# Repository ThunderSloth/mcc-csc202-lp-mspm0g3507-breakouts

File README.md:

# MCC CSC202 — LP-MSPM0G3507 Breakout Boards

KiCad project files and fabrication outputs for **breakout boards based on the TI MSPM0G3507 LaunchPad footprint** designed to fit dual- and triple-breadboard platforms (e.g., Jameco ValuePro) for use in Monroe Community College’s CSC-202 course.

---

## ℹ️  Hardware Documentation (MkDocs)

- **[Live Docs Site (renders + PDFs + iBOM + fabrication zips](https://thundersloth.github.io/mcc-csc202-lp-mspm0g3507-breakouts/)**  

---

## 📁 Boards

### **2-Term Breakout**
- [Docs Page](https://thundersloth.github.io/mcc-csc202-lp-mspm0g3507-breakouts/2-term/)
- [Download Gerbers (ZIP)](https://thundersloth.github.io/mcc-csc202-lp-mspm0g3507-breakouts/artifacts/2-term/fab/CSC202_LP_MSPM0G3507_2TERM_BREAKOUT_fab.zip)

---

### **3-Term Breakout**
- [Docs Page](https://thundersloth.github.io/mcc-csc202-lp-mspm0g3507-breakouts/3-term/)
- [Download Gerbers (ZIP)](https://thundersloth.github.io/mcc-csc202-lp-mspm0g3507-breakouts/artifacts/3-term/fab/CSC202_LP_MSPM0G3507_3TERM_BREAKOUT_fab.zip)

---

### **LED Display Module**
The CSC-202 LED Module is a visual output board featuring an 8-LED bar graph and a 4-digit seven-segment display. The LEDs and display segments can be driven either directly via GPIO (current sinking) or through an SPI shift register interface. A jumper shunt selects the control mode, allowing the module to demonstrate both parallel GPIO control and serial output expansion. The board is designed to plug directly into a standard breadboard for easy prototyping and lab use.
- [Docs Page](https://thundersloth.github.io/mcc-csc202-lp-mspm0g3507-breakouts/led-module/)
- [Download Gerbers (ZIP)](https://thundersloth.github.io/mcc-csc202-lp-mspm0g3507-breakouts/artifacts/led-module/fab/CSC202_LED_MODULE_fab.zip.zip)

---

### **DIP Switch / Pushbutton Module**
The CSC-202 DIP Switch / Pushbutton Module provides four digital input channels, each connected to both a DIP switch and a momentary pushbutton. This allows testing of both persistent and transient inputs on shared GPIO lines. An additional analog input is provided via an onboard potentiometer, which can be enabled or disconnected using a dedicated DIP switch. The module is designed for direct breadboard use and serves as a simple, reusable input interface for labs and debugging.

- [Docs Page](https://thundersloth.github.io/mcc-csc202-lp-mspm0g3507-breakouts/dipsw-module/)
- [Download Gerbers (ZIP)](https://thundersloth.github.io/mcc-csc202-lp-mspm0g3507-breakouts/artifacts/dipsw-module/fab/CSC202_DIPSW_fab.zip)

---

## 🛠 Repo Layout

- `hardware/pcb/kicad/` → KiCad source projects (per-board)
- `hardware/kibot/` → KiBot config
- `outputs/` → local generated artifacts (ignored/regen as needed)
- `docs/` + `docs/artifacts/` → MkDocs site + published artifacts

---

## 🔄 Generating outputs locally

If you want to regenerate all artifacts with KiBot + sync them into MkDocs:

```bash
make
```

---

## 📸 Fabricated Board Photos

<p align="center">
    <strong>3-Term Breakout</strong><br>
  
</p>

<p align="center">
  <strong>LED Display Module</strong><br>
  
</p>

---

## 📐 Example Breadboard Application

The diagram below shows an example application implemented on a 3-terminal breadboard.

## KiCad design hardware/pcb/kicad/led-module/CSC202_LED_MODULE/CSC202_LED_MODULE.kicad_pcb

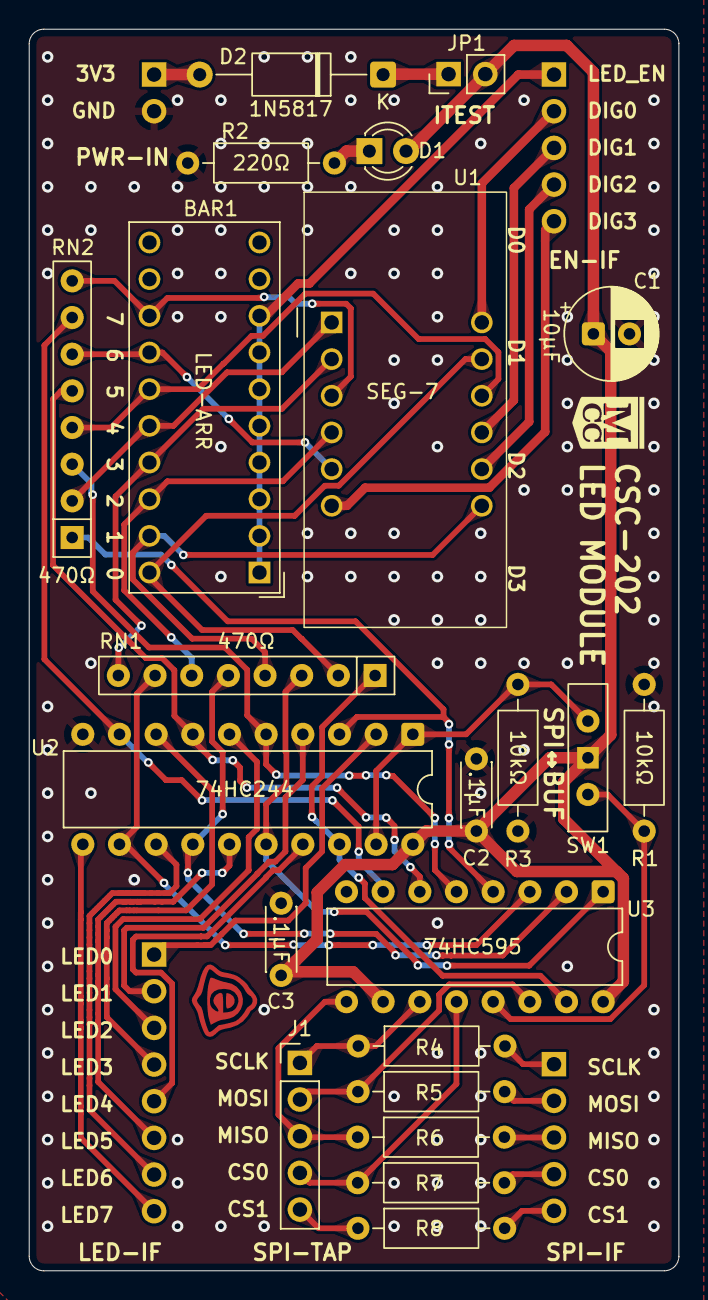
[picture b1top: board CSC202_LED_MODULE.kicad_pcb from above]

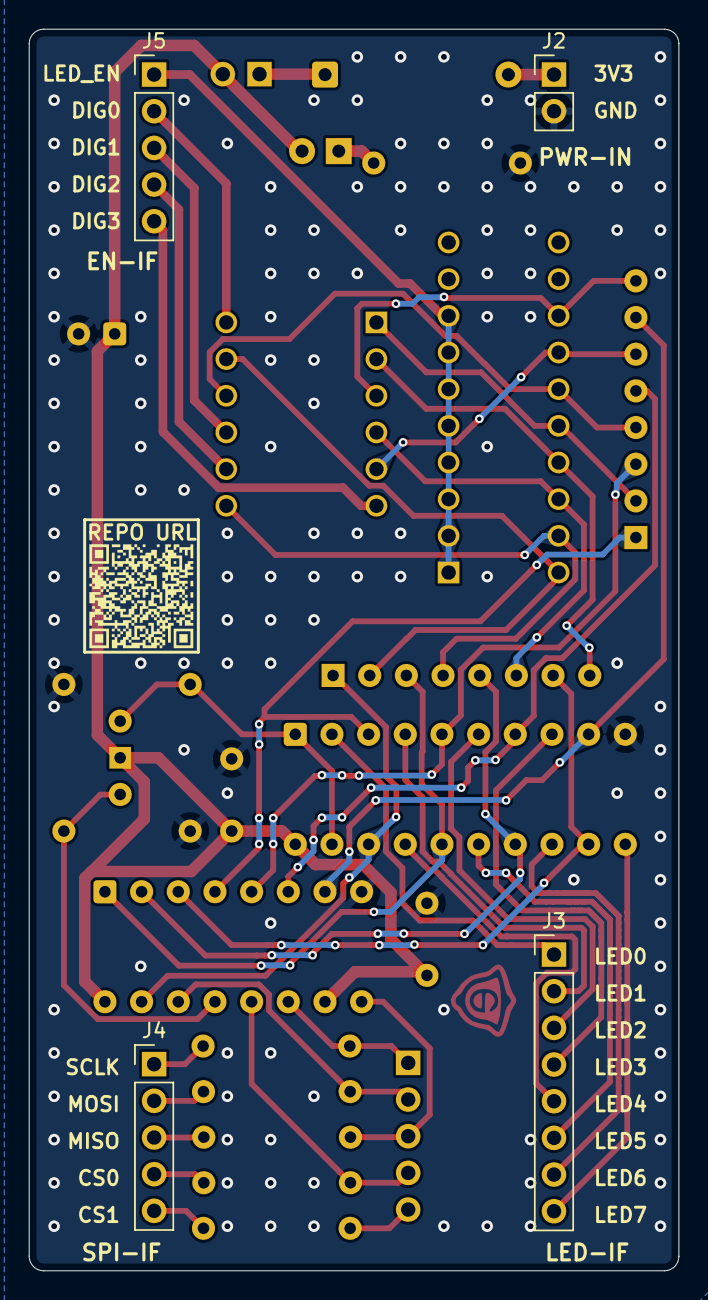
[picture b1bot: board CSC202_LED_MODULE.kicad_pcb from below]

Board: 2 copper layers, 45.0 x 86.0 mm, 26 parts (4 on the bottom side), 46 nets.

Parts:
BAR1: HDSP-4830_2; HDSP-4830
C1: 10µF; CP_Radial_D6.3mm_P2.50mm
C2, C3: .1µF; C_Disc_D4.3mm_W1.9mm_P5.00mm
D1: PWR; LED_D3.0mm
D2: 1N5817; D_A-405_P12.70mm_Horizontal
J1: SPI-TAP; PinHeader_1x05_P2.54mm_Vertical
J2: PWR-IN; PinHeader_1x02_P2.54mm_Vertical
J3: LED-IF; PinHeader_1x08_P2.54mm_Vertical
J4: SPI-IF; PinHeader_1x05_P2.54mm_Vertical
J5: EN-IF; PinHeader_1x05_P2.54mm_Vertical
JP1: TEST-PT; PinHeader_1x02_P2.54mm_Vertical
R1, R3: 10kΩ; R_Axial_DIN0207_L6.3mm_D2.5mm_P10.16mm_Horizontal
R2: 220Ω; R_Axial_DIN0207_L6.3mm_D2.5mm_P10.16mm_Horizontal
R4, R5, R6, R7, R8: 33Ω; R_Axial_DIN0207_L6.3mm_D2.5mm_P10.16mm_Horizontal
RN1, RN2: 470Ω; R_Array_SIP8
SW1: BUF↔SPI; SW_Slide-03_Wuerth-WS-SLTV_10x2.5x6.4_P2.54mm
U1: CA56-12SEKWA; CL3641BH
U2: 74HC244; DIP-20_W7.62mm
U3: 74HC595; DIP-16_W7.62mm

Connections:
+3V3: C1.1, C2.2, C3.2, D1.2 (A), JP1.2 (B), SW1.2 (B), U2.20 (VCC), U3.10 (~SRCLR), U3.16 (VCC)
/!BUF_EN: R3.1, SW1.3 (C), U2.1 (1OE), U2.19 (2OE)
/!SPI_EN: R1.1, SW1.1 (A), U3.13 (~OE)
/CLK: J1.1, R4.1, U3.11 (SRCLK)
/CLK_EXT: J4.1, R4.2
/CS0: J1.4, R7.1, U3.12 (RCLK)
/CS0_EXT: J4.4, R7.2
/CS1: J1.5, R8.1
/CS1_EXT: J4.5, R8.2
/DIG0: J5.2, U1.12 (CA1)
/DIG1: J5.3, U1.9 (CA2)
/DIG2: J5.4, U1.8 (CA3)
/DIG3: J5.5, U1.6 (CA4)
/LED_BUS0: RN1.1 (R1.1), U2.18 (1Y0), U3.15 (QA)
/LED_BUS1: RN1.3 (R2.1), U2.16 (1Y1), U3.1 (QB)
/LED_BUS2: RN1.5 (R3.1), U2.14 (1Y2), U3.2 (QC)
/LED_BUS3: RN1.7 (R4.1), U2.12 (1Y3), U3.3 (QD)
/LED_BUS4: RN2.1 (R1.1), U2.3 (2Y0), U3.4 (QE)
/LED_BUS5: RN2.3 (R2.1), U2.5 (2Y1), U3.5 (QF)
/LED_BUS6: RN2.5 (R3.1), U2.7 (2Y2), U3.6 (QG)
/LED_BUS7: RN2.7 (R4.1), U2.9 (2Y3), U3.7 (QH)
/LED_EN: BAR1.1 (A), BAR1.2 (A), BAR1.3 (A), BAR1.4 (A), BAR1.5 (A), BAR1.6 (A), BAR1.7 (A), BAR1.8 (A), J5.1
/LED_EXT0: J3.1, U2.2 (1A0)
/LED_EXT1: J3.2, U2.4 (1A1)
/LED_EXT2: J3.3, U2.6 (1A2)
/LED_EXT3: J3.4, U2.8 (1A3)
/LED_EXT4: J3.5, U2.17 (2A0)
/LED_EXT5: J3.6, U2.15 (2A1)
/LED_EXT6: J3.7, U2.13 (2A2)
/LED_EXT7: J3.8, U2.11 (2A3)
/LED_R0: BAR1.20 (K), RN1.2 (R1.2), U1.11 (a)
/LED_R1: BAR1.19 (K), RN1.4 (R2.2), U1.7 (b)
/LED_R2: BAR1.18 (K), RN1.6 (R3.2), U1.4 (c)
/LED_R3: BAR1.17 (K), RN1.8 (R4.2), U1.2 (d)
/LED_R4: BAR1.16 (K), RN2.2 (R1.2), U1.1 (e)
/LED_R5: BAR1.15 (K), RN2.4 (R2.2), U1.10 (f)
/LED_R6: BAR1.14 (K), RN2.6 (R3.2), U1.5 (g)
/LED_R7: BAR1.13 (K), RN2.8 (R4.2), U1.3 (DPX)
/MISO: J1.3, R6.1, U3.9 (QH')
/MISO_EXT: J4.3, R6.2
/MOSI: J1.2, R5.1, U3.14 (SER)
/MOSI_EXT: J4.2, R5.2
GND: C1.2, C2.1, C3.1, J2.2, R1.2, R2.1, R3.2, U2.10 (GND), U3.8 (GND)
unnamed: D1.1 (K), R2.2
unnamed: D2.2 (A), J2.1
unnamed: D2.1 (K), JP1.1 (A)

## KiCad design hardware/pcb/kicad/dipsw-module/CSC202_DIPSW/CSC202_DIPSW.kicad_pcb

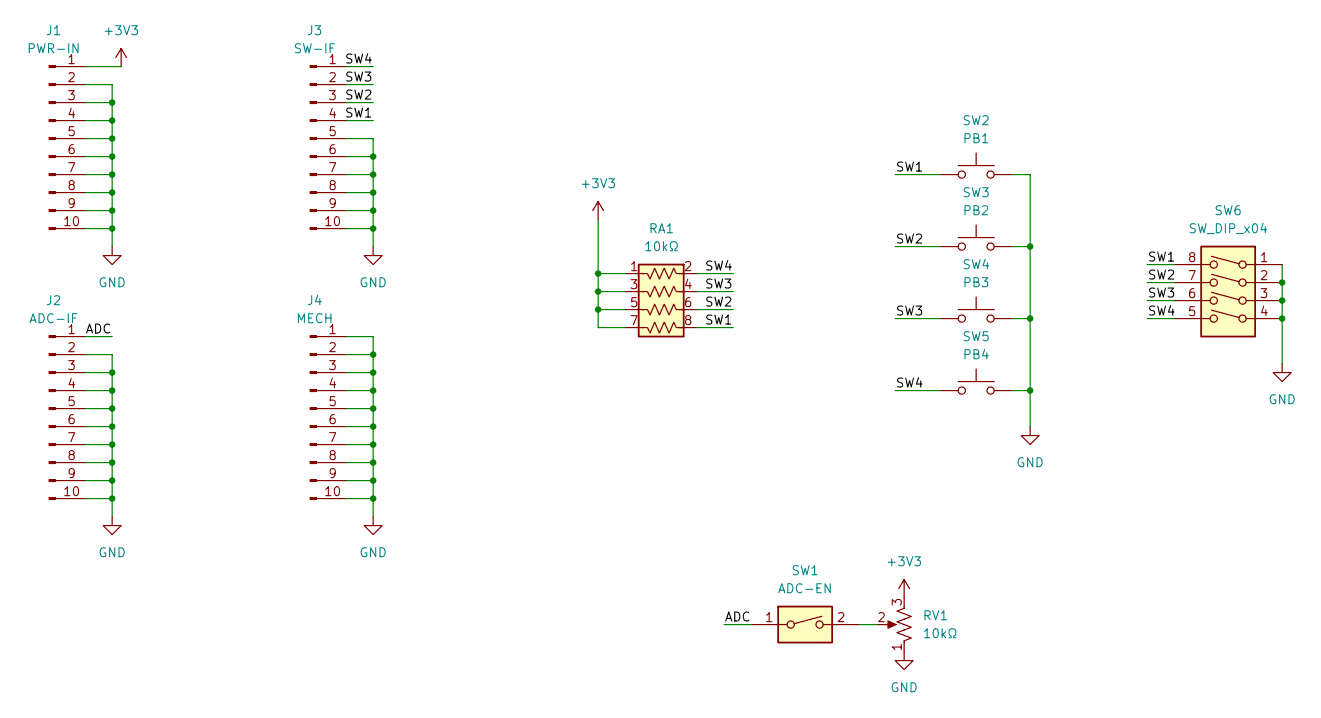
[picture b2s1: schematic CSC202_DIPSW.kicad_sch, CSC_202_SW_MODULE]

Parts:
J1: PWR-IN; PinHeader_1x10_P2.54mm_Vertical
J2: ADC-IF; PinHeader_1x10_P2.54mm_Vertical
J3: SW-IF; PinHeader_1x10_P2.54mm_Vertical
J4: MECH; PinHeader_1x10_P2.54mm_Vertical
RA1: 10kΩ; R_Array_SIP8
RV1: 10kΩ; Potentiometer_Piher_T-16H_Single_Horizontal
SW1: ADC-EN; SW_DIP_SPSTx01_Slide_9.78x4.72mm_W7.62mm_P2.54mm
SW2: PB1; SW_PUSH_6mm
SW3: PB2; SW_PUSH_6mm
SW4: PB3; SW_PUSH_6mm
SW5: PB4; SW_PUSH_6mm
SW6: SW_DIP_x04; SW_DIP_SPSTx04_Slide_9.78x12.34mm_W7.62mm_P2.54mm

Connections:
+3V3: J1.1, RA1.1 (R1a), RA1.3 (R2a), RA1.5 (R3a), RA1.7 (R4a), RV1.3 (1)
/ADC: J2.1, SW1.1
/SW1: J3.4, RA1.8 (R4b), SW2.2, SW6.8
/SW2: J3.3, RA1.6 (R3b), SW3.2, SW6.7
/SW3: J3.2, RA1.4 (R2b), SW4.2, SW6.6
/SW4: J3.1, RA1.2 (R1b), SW5.2, SW6.5
GND: J1.2, J1.3, J1.4, J1.5, J1.6, J1.7, J1.8, J1.9, J1.10, J2.2, J2.3, J2.4, J2.5, J2.6, J2.7, J2.8, J2.9, J2.10, J3.5, J3.6, J3.7, J3.8, J3.9, J3.10, J4.1, J4.2, J4.3, J4.4, J4.5, J4.6, J4.7, J4.8, J4.9, J4.10, RV1.1 (3), SW2.1, SW3.1, SW4.1, SW5.1, SW6.1, SW6.2, SW6.3, SW6.4
unnamed: RV1.2, SW1.2

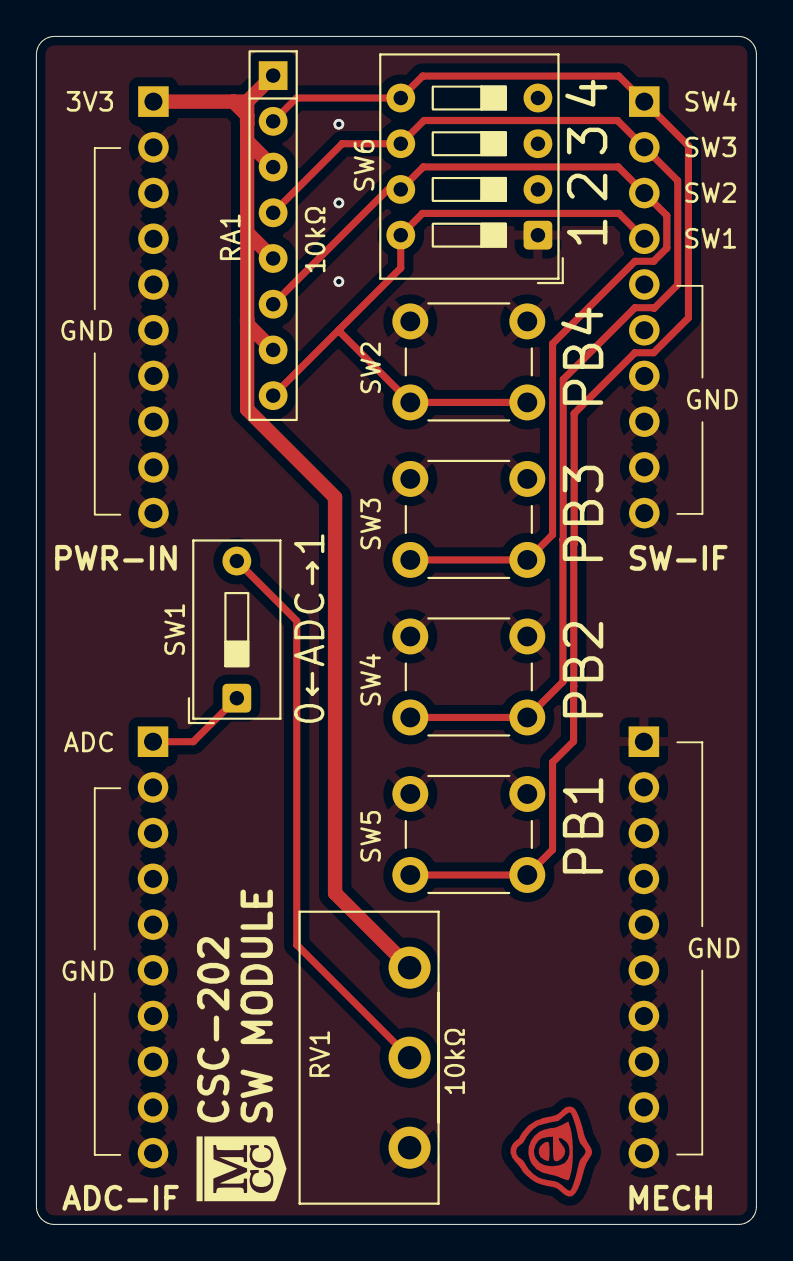
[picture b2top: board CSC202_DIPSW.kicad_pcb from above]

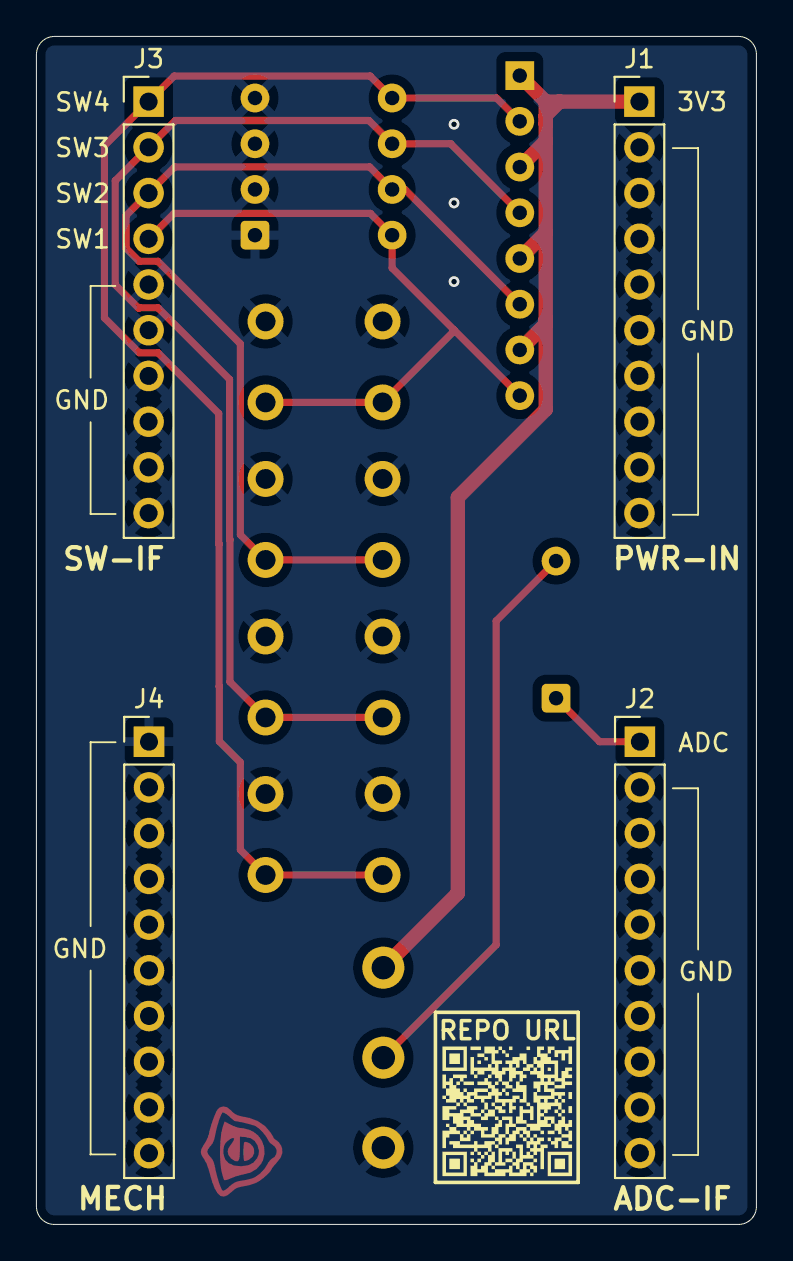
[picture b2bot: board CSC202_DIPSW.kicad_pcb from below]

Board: 2 copper layers, 40.0 x 66.0 mm, 12 parts (4 on the bottom side), 8 nets.

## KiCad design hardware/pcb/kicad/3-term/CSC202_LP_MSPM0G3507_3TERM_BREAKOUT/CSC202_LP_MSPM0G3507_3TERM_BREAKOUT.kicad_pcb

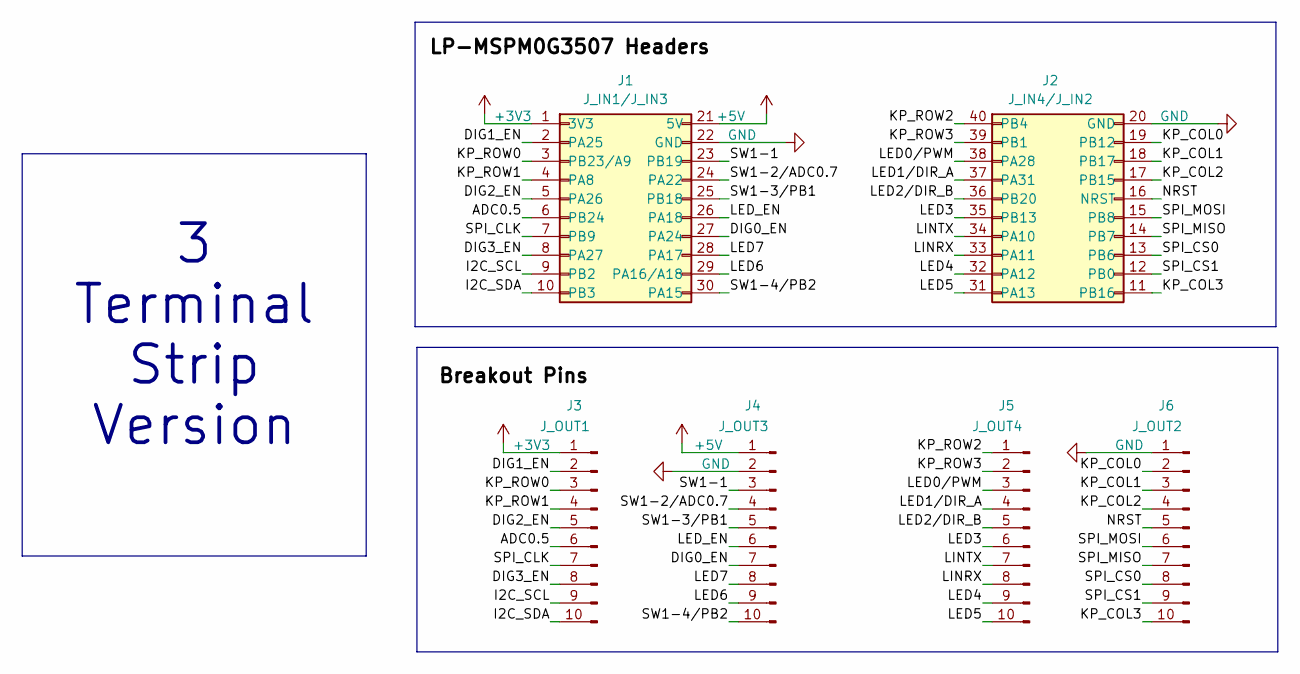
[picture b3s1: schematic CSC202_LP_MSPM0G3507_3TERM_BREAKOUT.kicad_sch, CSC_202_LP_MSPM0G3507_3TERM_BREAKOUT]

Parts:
J1: J_IN1/J_IN3; PinHeader_2x10_P2.54mm_Vertical
J2: J_IN4/J_IN2; PinHeader_2x10_P2.54mm_Vertical
J3: J_OUT1; PinHeader_1x10_P2.54mm_Vertical
J4: J_OUT3; PinHeader_1x10_P2.54mm_Vertical
J5: J_OUT4; PinHeader_1x10_P2.54mm_Vertical
J6: J_OUT2; PinHeader_1x10_P2.54mm_Vertical

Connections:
+3V3: J1.1 (3V3), J3.1
+5V: J1.21 (5V), J4.1
/ADC0.5: J1.6 (PB24), J3.6
/DIG0_EN: J1.27 (PA24), J4.7
/DIG1_EN: J1.2 (PA25), J3.2
/DIG2_EN: J1.5 (PA26), J3.5
/DIG3_EN: J1.8 (PA27), J3.8
/I2C_SCL: J1.9 (PB2), J3.9
/I2C_SDA: J1.10 (PB3), J3.10
/KP_COL0: J2.19 (PB12), J6.2
/KP_COL1: J2.18 (PB17), J6.3
/KP_COL2: J2.17 (PB15), J6.4
/KP_COL3: J2.11 (PB16), J6.10
/KP_ROW0: J1.3 (PB23/A9), J3.3
/KP_ROW1: J1.4 (PA8), J3.4
/KP_ROW2: J2.40 (PB4), J5.1
/KP_ROW3: J2.39 (PB1), J5.2
/LED0/PWM: J2.38 (PA28), J5.3
/LED1/DIR_A: J2.37 (PA31), J5.4
/LED2/DIR_B: J2.36 (PB20), J5.5
/LED3: J2.35 (PB13), J5.6
/LED4: J2.32 (PA12), J5.9
/LED5: J2.31 (PA13), J5.10
/LED6: J1.29 (PA16/A18), J4.9
/LED7: J1.28 (PA17), J4.8
/LED_EN: J1.26 (PA18), J4.6
/LINRX: J2.33 (PA11), J5.8
/LINTX: J2.34 (PA10), J5.7
/NRST: J2.16 (NRST), J6.5
/SPI_CLK: J1.7 (PB9), J3.7
/SPI_CS0: J2.13 (PB6), J6.8
/SPI_CS1: J2.12 (PB0), J6.9
/SPI_MISO: J2.14 (PB7), J6.7
/SPI_MOSI: J2.15 (PB8), J6.6
/SW1-1: J1.23 (PB19), J4.3
/SW1-2/ADC0.7: J1.24 (PA22), J4.4
/SW1-3/PB1: J1.25 (PB18), J4.5
/SW1-4/PB2: J1.30 (PA15), J4.10
GND: J1.22 (GND), J2.20 (GND), J4.2, J6.1

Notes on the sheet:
3 Terminal Strip Version

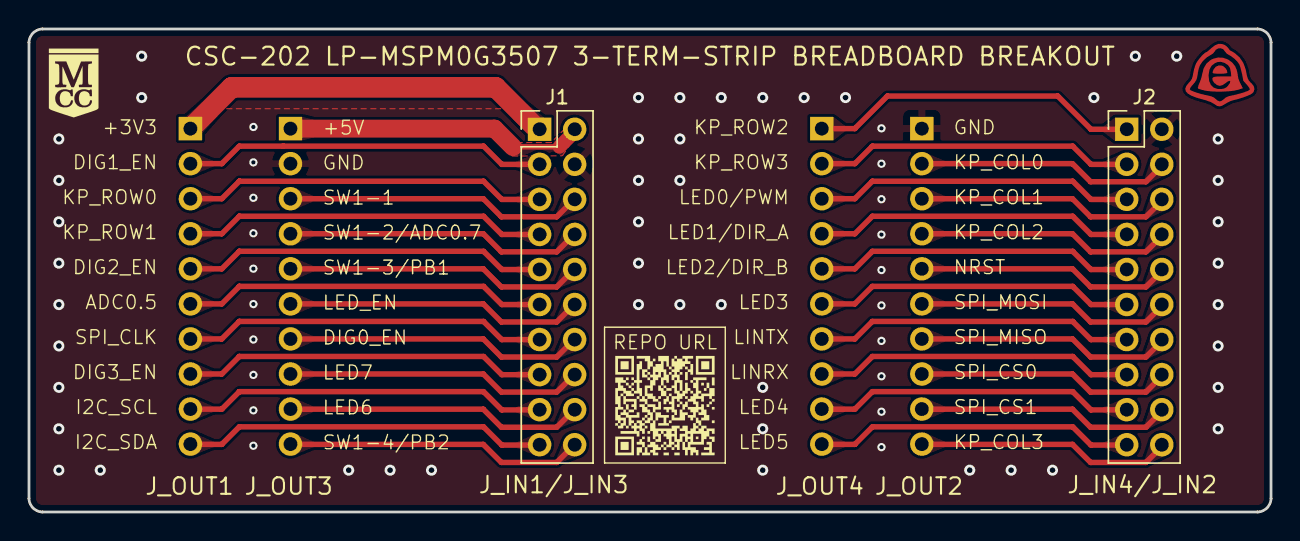
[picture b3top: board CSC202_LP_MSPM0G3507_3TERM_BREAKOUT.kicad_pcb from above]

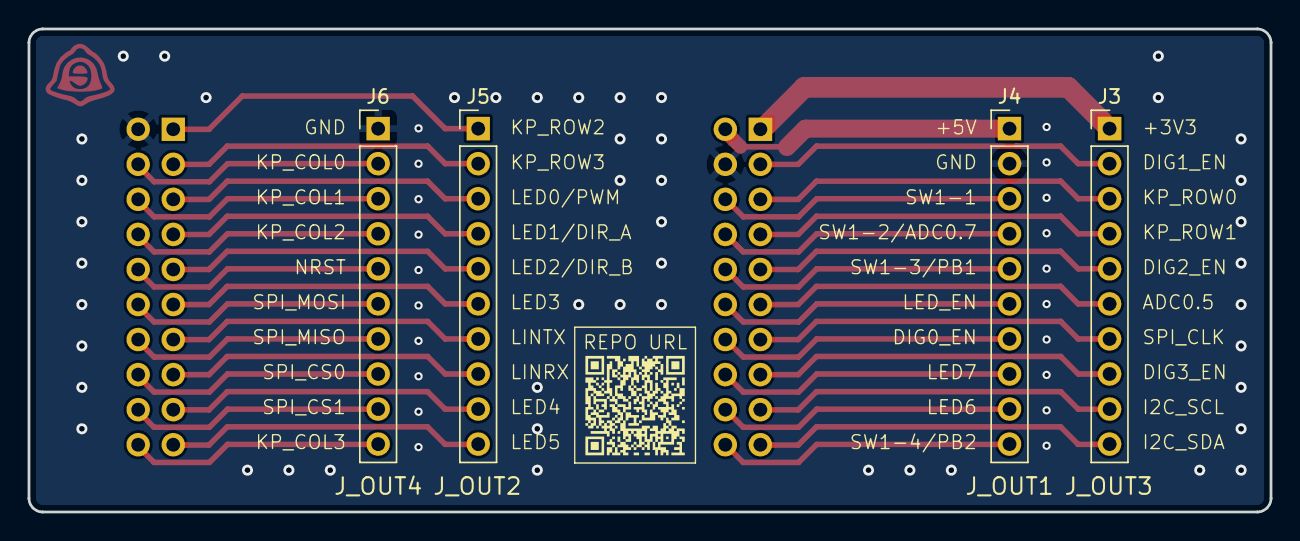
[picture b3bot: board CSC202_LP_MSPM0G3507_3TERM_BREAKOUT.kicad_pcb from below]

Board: 2 copper layers, 90.0 x 35.0 mm, 9 parts (5 on the bottom side), 39 nets.

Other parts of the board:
G1, G2: LOGO; Repo_URL_QR
LOGO1: LOGO; MCC-Logo

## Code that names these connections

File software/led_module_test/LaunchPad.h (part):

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#define LED2_PORT (GPIO_PORTB)
#define LED2_MASK (1 << 20)
#define LED2_IOMUX (IOMUX_PINCM48)
#define LED3_PORT (GPIO_PORTB)
#define LED3_MASK (1 << 13)
#define LED3_IOMUX (IOMUX_PINCM30)
#define LED4_PORT (GPIO_PORTA)
#define LED4_MASK (1 << 12)
#define LED4_IOMUX (IOMUX_PINCM34)
#define LED5_PORT (GPIO_PORTA)
#define LED5_MASK (1 << 13)
#define LED5_IOMUX (IOMUX_PINCM35)
#define LED6_PORT (GPIO_PORTA)
#define LED6_MASK (1 << 16)
#define LED6_IOMUX (IOMUX_PINCM38)
#define LED7_PORT (GPIO_PORTA)
#define LED7_MASK (1 << 17)
#define LED7_IOMUX (IOMUX_PINCM39)

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#define DIP_SW4_IOMUX (IOMUX_PINCM37)

// Defines for Keypad switches
#define KP_COL0_PORT (GPIO_PORTB)
#define KP_COL0_MASK (1 << 12)
#define KP_COL0_IOMUX (IOMUX_PINCM29)
#define KP_COL1_PORT (GPIO_PORTB)
#define KP_COL1_MASK (1 << 17)
#define KP_COL1_IOMUX (IOMUX_PINCM43)
#define KP_COL2_PORT (GPIO_PORTB)
#define KP_COL2_MASK (1 << 15)
#define KP_COL2_IOMUX (IOMUX_PINCM32)
#define KP_COL3_PORT (GPIO_PORTB)
#define KP_COL3_MASK (1 << 16)
#define KP_COL3_IOMUX (IOMUX_PINCM33)
#define KP_ROW0_PORT (GPIO_PORTB)
#define KP_ROW0_MASK (1 << 23)
#define KP_ROW0_IOMUX (IOMUX_PINCM51)
#define KP_ROW1_PORT (GPIO_PORTA)
#define KP_ROW1_MASK (1 << 8)
#define KP_ROW1_IOMUX (IOMUX_PINCM19)
#define KP_ROW2_PORT (GPIO_PORTB)
#define KP_ROW2_MASK (1 << 4)
#define KP_ROW2_IOMUX (IOMUX_PINCM17)
#define KP_ROW3_PORT (GPIO_PORTB)
#define KP_ROW3_MASK (1 << 1)
#define KP_ROW3_IOMUX (IOMUX_PINCM13)

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#define I2C_INST_IRQHandler I2C1_IRQHandler
#define I2C_INST_INT_IRQN I2C1_INT_IRQn
#define I2C_BUS_SPEED_HZ 100000
#define I2C_SDA_PORT (GPIO_PORTB)
#define I2C_SDA_MASK (1 << 3)
#define I2C_SDA_IOMUX (IOMUX_PINCM16)
#define I2C_SDA_PINCM_IOMUX_FUNC (IOMUX_PINCM16_PF_I2C1_SDA)
#define I2C_SCL_PORT (GPIO_PORTB)
#define I2C_SCL_MASK (1 << 2)
#define I2C_SCL_IOMUX (IOMUX_PINCM15)
#define I2C_SCL_PINCM_IOMUX_FUNC (IOMUX_PINCM15_PF_I2C1_SCL)
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
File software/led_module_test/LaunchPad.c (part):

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
// Define the configuration data for the IIC port on the CSC202 Board
const i2c_struct iic_config_data[] = {
        {I2C_SDA_PORT, I2C_SDA_MASK, I2C_SDA_IOMUX, I2C_SDA_PINCM_IOMUX_FUNC},
        {I2C_SCL_PORT, I2C_SCL_MASK, I2C_SCL_IOMUX, I2C_SCL_PINCM_IOMUX_FUNC}
};

// ----------------------------------------------------
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// -----------------------------------------------------------------------------
void  dipsw_filter_enable(void)
{
  // SW1 is PB19
  GPIOB->FILTEREN31_16 |= GPIO_FILTEREN31_16_DIN19_EIGHT_CYCLE;
  
  // SW2 is PA22
  GPIOA->FILTEREN31_16 |= GPIO_FILTEREN31_16_DIN22_EIGHT_CYCLE;
  
  // PB1 is PB18
  GPIOB->FILTEREN31_16 |= GPIO_FILTEREN31_16_DIN18_EIGHT_CYCLE;
  
  // SW2 is PA22
  GPIOA->FILTEREN15_0 |= GPIO_FILTEREN15_0_DIN15_EIGHT_CYCLE;
  
  // for (uint8_t sw_idx = 0; sw_idx < MAX_NUM_DIPSW; sw_idx++)
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// -----------------------------------------------------------------------------
void motor0_init(void)
{
  // Set PA28 (LD0) for TIMA0_C3
  IOMUX->SECCFG.PINCM[LED0_IOMUX] = IOMUX_PINCM3_PF_TIMA0_CCP3 | 
                                    IOMUX_PINCM_PC_CONNECTED;

  // Set PA31 (LD1) for output
  IOMUX->SECCFG.PINCM[LED1_IOMUX] = PINCM_GPIO_PIN_FUNC | 
                                    IOMUX_PINCM_PC_CONNECTED;
  GPIOA->DOESET31_0 = LED1_MASK;

  // Set PB20 (LD2) for output
  IOMUX->SECCFG.PINCM[LED2_IOMUX] = PINCM_GPIO_PIN_FUNC | 
                                    IOMUX_PINCM_PC_CONNECTED;
  GPIOA->DOESET31_0 = LED2_MASK;
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
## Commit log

2025-09-23 3-term complete
2025-09-30 completed 2-term version
2025-09-30 update pictures
2025-09-30 update png
2025-09-30 adjust relative photo sizes
2025-10-21 board fabricated
2025-10-21 Add image of 3-Terminal Version on Breadboard
2026-01-15 Restructure repo for KiBot + MkDocs workflow
2026-01-16 implemented kibot and mkdocs
2026-01-16 Revise README with detailed project information
    Updated README to include hardware documentation, board details, and repo layout.
2026-01-16 Clean up formatting in README.md
    Remove unnecessary horizontal lines from README.
2026-02-16 example application
2026-02-16 Add example breadboard application to README
    Added an example breadboard application section with a diagram.
2026-03-05 init led module
2026-03-05 rename screenshot
2026-03-05 Add LED Display Module section to README
    Added section for the LED Display Module with details and links.
2026-03-05 added side-by-side front/bottom renders to mkdocs homepage for the led module board
2026-03-05 Enhance LED Module description with prototyping details
    Added details about breadboard compatibility for easy prototyping.
2026-03-06 added reverse polarity protection and included bottom assy in outputs
2026-03-06 fixed broken link issue in index.md
2026-03-07 restore repository contents
2026-04-01 add DIP switch + pushbutton module (pcb, docs, outputs)
2026-04-01 add switch module 3D render
2026-04-01 improve repo cleanup and docs generation tooling
2026-04-01 add MSPM0 LED module test project
2026-04-01 add DIP switch module KiCad design
2026-04-01 add DIP switch module generated artifacts and docs page
2026-04-01 update LED module KiCad design
2026-04-01 regenerate LED module artifacts
2026-04-01 regenerate 2-term and 3-term breakout artifacts
2026-04-01 update MkDocs navigation for module docs
2026-04-01 Add DIP Switch / Pushbutton Module section to README
    Added details about the DIP Switch / Pushbutton Module, including its features and links to documentation and downloads.
2026-04-01 add fabricated led module photo
2026-04-01 replace fabricated led module photo
2026-04-01 Revise fabricated board photo section
    Updated section title and added photo of LED Display Module.
2026-04-07 note added to sch concerning backpowering
2026-04-07 update outputs

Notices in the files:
software/led_module_test/LaunchPad.c:
Copyright (c) 2024 by Bruce Link
